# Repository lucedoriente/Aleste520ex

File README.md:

# Aleste 520EX — Western Through-Hole (THT) Complete System (KiCad 9.0)

🌐 **Language / Lingua**: **🇬🇧 English** | [**🇮🇹 Leggi in Italiano (`README.it.md`)**](README.it.md)

---

Complete Western hardware reproduction of the **1993 Soviet Aleste 520EX** Z80 personal computer (an Amstrad CPC 6128 & MSX2 compatible hybrid architecture designed by Patisonic in Omsk, Russia), completely redesigned in **KiCad 9.0** using **100% Western Through-Hole (THT)** components, complete with its dedicated **Cherry MX Mechanical Keyboard (`keyboard/`)** and **Parametric Anti-Flex Enclosure (`case/`)**.

---

## 1. Repository Structure

The repository is organized into four modular directories:

| Directory | Contents | Description |
| :--- | :--- | :--- |
| **[`board/`](board/)** | `Aleste520v4.kicad_pro`, `.kicad_sch`, `.kicad_pcb`, `Componenti_Aleste520v4.csv` | **Motherboard (`400.9 × 280.5 mm`)**: 100% Western THT ICs (`U1..U89`), standard `2.54 mm` `2x06` keyboard headers (`X8`, `X9`), 11 `M3` mounting holes (`MH1..MH11`), labeled power/RTC pads (`P1..P8`), **0 ERC / 0 DRC errors**. |
| **[`keyboard/`](keyboard/)** | `Aleste520_Keyboard.kicad_pro`, `.kicad_sch`, `.kicad_pcb`, `Componenti_Tastiera_Aleste520.csv`, [`README.md`](keyboard/README.md) | **Mechanical Keyboard (`358.0 × 122.0 mm`)**: 82 Cherry MX switches (`SW1..SW81` matrix + `SW82` Hardware Reset), 81 `1N4148` anti-ghosting diodes (Full NKRO), standard `2.54 mm` `2x06` IDC headers (`J1`, `J2`), 10 `M3` anti-flex mounting holes (`MH1..MH10`), **0 ERC / 0 DRC errors**. |
| **[`case/`](case/)** | `Aleste520_Case.FCStd`, `Aleste520_Case.step`, `keyboard_plate.dxf`, [`README.md`](case/README.md) | **Custom Desktop Enclosure (`416.0 × 296.0 × 62.0 mm`)**: Native FreeCAD 1.1 3D CAD project (`Aleste520_Case.FCStd`, `Aleste520_Bottom_Case.FCStd`, `Aleste520_Top_Cover.FCStd`, `Aleste520_Switch_Plate.FCStd`, `Aleste520_Case.step`) (Bottom Base Tray, Sloped Top Cover, `1.5 mm` Switch Mounting Plate, and 4-quadrant split mode for standard $256\times 256\text{ mm}$ 3D printers) + laser-cut ready `keyboard_plate.dxf` with a **3-Stage Anti-Flex Keyboard Support System**. |
| **[`rom/`](rom/)** | `AL512.BIN`, `RFCOLDAT.BIN`, `RFVDKEY.BIN`, `MAPPER.BIN`, `ROMRAM.BIN`, `AF.BIN` | **Original Firmware Images**: 100% bit-compatible with this Western hardware reproduction (English boot menu, standard ASCII/Latin + Cyrillic support). |

---

## 2. Motherboard Highlights (`board/`)

* **100% Western IC Conversion (`U1..U89`)**:
  * All Soviet logic, memory, and peripheral ICs have been converted to standard Western equivalents (`74LSxx`, `74HCxx`, `Z80CPU`, `8255`, `8253`, `8251A`, `8272`, `MC6845`, `AY-3-8910`, `MC146818P`, `HM50256P-20` / `41256`).
  * **Resolved `KR1802IR1` (`КР1802ИР1`)**: Replaced the scarce Soviet 24-pin 16×4 two-port register file ICs at `U60`, `U61`, `U82`, and `U83` with the Western **AMD `AM29705` (DIP-28)**, properly wiring its dual address buses (`A0..A3`, `B0..B3`), write strobes (`~WE1`, `~WE2`), transparent output latches (`~A-LO = GND`, `LE = VCC`), and open-collector outputs (`~OE-A`) for both the color palette (`U60`+`U61`) and keyboard/mapper subsystem (`U82`+`U83`).
  * Standardized all IC reference designators from Russian `D1..D89` to Western `U1..U89`.
* **Upgraded Standard $2.54\text{ mm}$ Keyboard Connectors (`X8` & `X9`)**:
  * Replaced the obsolete single-row $1.27\text{ mm}$ pitch headers on `X8` and `X9` with standard **$2.54\text{ mm}$ ($0.1''$) dual-row `2x06` Pin Headers / IDC Box Headers** (`Connector_PinHeader_2.54mm:PinHeader_2x06_P2.54mm_Vertical`), compatible with standard 12-pin $1.27\text{ mm}$ flat ribbon IDC cables or DuPont harnesses.
* **11 Mechanical `M3` Mounting Holes (`MH1..MH11`)**:
  * Added 11 plated `M3` ($\varnothing\ 3.2\text{ mm}$ drill, $\varnothing\ 6.0\text{ mm}$ pad tied to `GND` chassis shield) mounting holes along the perimeter, center, and front keyboard zone to bolt the motherboard to the enclosure standoffs and coaxial keyboard anti-flex support towers.
* **Fully Routed 2-Layer PCB (`400.9 × 280.5 mm`)**:
  * **0 ERC Errors** across the hierarchical schematic (`board/Aleste520v4.kicad_sch` + 6 sub-sheets).
  * **0 DRC Violations & 0 Unconnected Items** on the PCB (`board/Aleste520v4.kicad_pcb`).
  * Full `F.Cu` and `B.Cu` `GND` copper pours with **Thermal Reliefs** (`0.35 mm` spokes, `0.25 mm` gap) and over **3,670 GND stitching vias**, plus 95 local `100 nF` decoupling capacitors (`C32..C128`).

---

## 3. Power Supply Guide: PicoPSU + $220\text{ V AC} \rightarrow 12\text{ V DC}$

The Aleste 520EX motherboard is powered primarily by **`+5V DC`** (`VCC` plane, consuming $\approx 2.2\text{ A} \dots 2.8\text{ A}$ for the 89 TTL/CMOS/NMOS ICs) plus **`+12V DC`** (routed to the expansion slot `X1` and video connector `X5.B1`), while a separate **`3V` Lithium Coin Cell (`CR2032`)** backs up the `MC146818P` Real-Time Clock (`U19`).

### 3.1 Safe Connection to $220\text{ V AC}$ Mains
For complete electrical safety (eliminating any high-voltage $220\text{ V AC}$ inside the 3D-printed enclosure):
1. **External AC/DC Brick ($220\text{ V AC} \rightarrow 12\text{ V DC}$)**: Use a certified external **`12V DC / 5A (60W)`** switching power adapter with a standard `5.5 × 2.5 mm` DC barrel plug.
2. **Internal DC-DC PicoPSU (`PicoPSU-80` / `PicoPSU-120` or `12V->5V 5A` Buck)**:
   * Mount the panel-mount `5.5 × 2.5 mm` DC barrel jack and optional rocker switch into the dedicated rear cutouts provided in [`case/Aleste520_Case.FCStd`](case/Aleste520_Case.FCStd).
   * Connect the `PS_ON#` (Green wire, Pin 16 on the ATX 24-pin header) of the PicoPSU to `GND` (Black wire, Pin 15/17) via the rear power switch so the PicoPSU turns on when switched.
   * Feed `+5V` and `+12V` from the PicoPSU (using the 4-pin Molex / SATA power cable or ATX header) to the motherboard pads `P1..P6` as detailed below.

### 3.2 Motherboard Power & RTC Battery Pads (`P1..P8`)

| Pad | Silkscreen Label | Net | PCB Coordinates `(X, Y)` | Connection |
| :--- | :--- | :--- | :--- | :--- |
| **`P1`** | `+5V_VCC` | `VCC` (`+5V`) | `(321.31, 240.03)` | **PicoPSU `+5V` (Red wire, 18 AWG)** — Main logic supply |
| **`P2`** | `GND_PWR` | `GND` | `(311.15, 250.19)` | **PicoPSU `GND` (Black wire, 18 AWG)** — Main ground return |
| **`P3`** | `+12V_EXP` | `+12V` | `(303.53, 250.19)` | **PicoPSU `+12V` (Yellow wire)** — Expansion slot `X1` & `X5.B1` |
| **`P4`** | `GND_EXP` | `GND` | `(295.91, 250.19)` | **PicoPSU `GND` (Black wire)** — Auxiliary ground return |
| **`P5`** | `+5V_AUX` | `VCC` (`+5V`) | `(292.10, 260.35)` | **PicoPSU `+5V` (Red wire)** — Parallel `+5V` feed (reduces voltage drop) |
| **`P6`** | `GND_AUX` | `GND` | `(306.07, 265.43)` | **PicoPSU `GND` (Black wire)** — Parallel `GND` feed |
| **`P7`** | `BAT+_3V` | `3V` (`MC146818` RTC) | `(330.20, 232.41)` | **`CR2032` Coin Cell Holder `+` (Positive)** — RTC CMOS backup **(`3V` ONLY!)** |
| **`P8`** | `BAT-_GND` | `GND` | `(330.20, 226.06)` | **`CR2032` Coin Cell Holder `-` (Negative)** — RTC ground |

---

## 4. Dedicated Mechanical Keyboard (`keyboard/`)

See [**`keyboard/README.md`**](keyboard/README.md) for the complete keyboard documentation, matrix table, and pinout.

* **PCB Dimensions**: `358.0 × 122.0 mm` (2-layer FR4, `1.6 mm`, **0 ERC / 0 DRC violations**).
* **Switches**: 81 Cherry MX keys (`SW1..SW81`) arranged in the native $11 \times 8$ Aleste 520EX matrix (`KM0..KM10` $\times$ `KM11..KM18`) + 1 Cherry MX Hardware Reset key (`SW82`, `SBRES` $\rightarrow$ `GND`).
* **Full NKRO Anti-Ghosting**: 81 through-hole `1N4148` diodes (`D1..D81`, `DO-35`) with cathode (`Pin 1`) on column `KM0..KM10` and anode (`Pin 2`) on switch `Pin 1` (matched to the active-low column strobe driven by `74LS145` `U80`).
* **1:1 Ribbon Cable Connection**: Two `2x06` ($2.54\text{ mm}$ pitch) headers `J1` and `J2` connect straight to motherboard headers `X8` and `X9`.

---

## 5. Custom Enclosure with Anti-Flex Keyboard Support (`case/`)

See [**`case/README.md`**](case/README.md) for printing, laser-cutting, and assembly instructions.

* **External Dimensions**: `416.0 × 296.0 × 62.0 mm` (wedged profile: `32 mm` front typing height, `62 mm` rear I/O panel height).
* **3-Stage Anti-Flex Keyboard Support System** (eliminating typing deflection across the $358\text{ mm}$ span):
  1. **`1.5 mm` Rigid Switch Mounting Plate** (`case/keyboard_plate.dxf` for laser-cut aluminum/steel/FR4, or 3D-printed from `case/Aleste520_Switch_Plate.FCStd`).
  2. **Orthogonal Internal Stiffening Grid** built into the underside of the Top Cover (`4.0 × 8.0 mm` perimeter ledge + 2 transverse ribs + 2 longitudinal ribs).
  3. **7 Coaxial Anti-Flex Support Columns (`MH5..MH11`)** transferring vertical typing force straight through the Keyboard PCB (`MH1..MH10`) and Motherboard (`MH5..MH11`) down to the Bottom Case floor.

---

## 6. EPROM & Bipolar PROM Programming Guide (`rom/`)

All 6 original binary files in the [`rom/`](rom/) directory are **100% bit-for-bit compatible** with this Western PCB: no address or data lines were swapped during PCB layout, and the `AM29705` replacements (`U60`, `U61`, `U82`, `U83`) operate in non-inverting transparent mode identical to the original `KR1802IR1`.

> **🇬🇧 Note on Language**: The `rom/AL512.BIN` firmware already features its built-in **English boot/setup interface** (`ALESTE 520EX`, `PATISONIC 1993`, `SETUP`) and includes both standard **Western Latin/ASCII** and Cyrillic character sets (`RUS/LAT` key).

### 6.1 Firmware Mapping Table

| Binary File | Size | PCB Socket | Western IC (Target) | Compatible Equivalents | Original Soviet IC | Function |
| :--- | :--- | :--- | :--- | :--- | :--- | :--- |
| [`rom/AL512.BIN`](rom/AL512.BIN) | `65,536 B` (64 KB) | **`U31`** | **`27C512`** (DIP-28) | `M27C512`, `AM27C512`, `W27C512` (EEPROM) | `К573РФ4` (`K573RF4`) | System BIOS, BASIC, Boot & AMSDOS |
| [`rom/RFCOLDAT.BIN`](rom/RFCOLDAT.BIN) | `2,048 B` (2 KB) | **`U62`** | **`2716` / `27C16`** (DIP-24) | `TMS27C16`, `M2716`, **`AT28C16`** (EEPROM) | `К573РФ2` (`K573RF2`) | Color Palette Lookup (`XD0..XD5`, `VRAMACC`) |
| [`rom/RFVDKEY.BIN`](rom/RFVDKEY.BIN) | `2,048 B` (2 KB) | **`U65`** | **`2716` / `27C16`** (DIP-24) | `TMS27C16`, `M2716`, **`AT28C16`** (EEPROM) | `К573РФ2` (`K573RF2`) | Video Sync (`SYNC*`, `HY*`, `SINT*`) & Keyboard Scan (`KK0..KK3`) |
| [`rom/MAPPER.BIN`](rom/MAPPER.BIN) | `256 B` (`256×4` bit) | **`U28`** | **`AM27S20`** (DIP-16 OC) | `N82S129`, `SN74S287`, `MMI6301`, `MB7052` | `КР556РТ4` (`KR556RT4`) | Memory Bank Address Mapper (`MAP14..MAP17`) |
| [`rom/ROMRAM.BIN`](rom/ROMRAM.BIN) | `256 B` (`256×4` bit) | **`U67`** | **`AM27S20`** (DIP-16 OC) | `N82S129`, `SN74S287`, `MMI6301`, `MB7052` | `КР556РТ4` (`KR556RT4`) | Bus & Memory Enable Decoder (`/ROMEN`, `/RAMEN`, `BUFFER0..1`) |
| [`rom/AF.BIN`](rom/AF.BIN) | `32 B` (`32×8` bit) | **`U69`** | **`SN74188`** (DIP-16 OC) | `N82S23`, `AM27S18`, `MMI6330`, `TBP18SA030` | `К155РЕ3` (`K155RE3`) | Floppy Disk Controller State / Precompensation PROM |

> **⚠️ Critical Note on Output Type (`U28`, `U67`, `U69`)**: The original schematic uses **Open-Collector (OC)** bipolar PROMs (`82S129` / `AM27S20` for `U28`, `U67` and `82S23` / `SN74188` for `U69`). For `U28` (`MAPPER.BIN`), pin 13 (`CS1`) is driven by `/MAPBLK` and the outputs `MAP14..MAP17` are wire-ORed with open-collector register files `U87`/`U88` (`74LS170`), so **`U28` MUST be an Open-Collector part** (`AM27S20` / `82S129` / `74S287`, **not** the totem-pole `82S126` / `74S387` / `AM27S21`).

### 6.2 Required Materials & Tools

* **For the 3 MOS EPROMs / EEPROMs (`U31`, `U62`, `U65`)**:
  * **1× `27C512` (DIP-28, $\le 150\text{ ns}$)** for **`U31`** (e.g., Winbond `W27C512-45Z` EEPROM or ST `M27C512-10F1`).
  * **2× `AT28C16-15PC` (DIP-24 EEPROM, 150 ns)** or fast CMOS `27C16` for **`U62`** and **`U65`** (`AT28C16` is 100% plug-and-play in `U62`/`U65` because Pin 21 is tied to `+5V`, and programs at 5V on any USB programmer such as **XGecu TL866II Plus / T48 / T56**).
* **For the 3 Bipolar Fuse-Link PROMs (`U28`, `U67`, `U69`)**:
  * **2× `82S129` / `AM27S20` / `SN74S287` (DIP-16, 256×4 OC)** for **`U28`** and **`U67`**.
  * **1× `82S23` / `SN74188` / `AM27S18` (DIP-16, 32×8 OC)** for **`U69`**.
  * **Programmer**: Industrial programmer supporting bipolar fuse PROMs (**Data I/O**, **Hi-Lo ALL-03/07/11**, **Elnec BeeProg**, **Stag PP39/42**) or an open-source **Arduino Bipolar PROM Programmer**.

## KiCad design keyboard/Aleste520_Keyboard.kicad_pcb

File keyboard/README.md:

# Aleste 520EX — Staggered Mechanical Keyboard Subsystem (`keyboard/`)

This directory contains the complete KiCad 9.0 schematic, routed 2-layer PCB, 3D switch/stabilizer models, and Bill of Materials for the **Aleste 520EX Staggered Mechanical Keyboard** (`358.0 × 122.0 mm`), reverse-engineered directly from the hardware keyboard scan EPROM ([`rom/RFVDKEY.BIN`](../rom/RFVDKEY.BIN), IC `U65`) and system BIOS ([`rom/AL512.BIN`](../rom/AL512.BIN), offset `0x1EEF`).

---

## 1. Files in `keyboard/`

- **[`Aleste520_Keyboard.kicad_pro`](Aleste520_Keyboard.kicad_pro)**: KiCad 9.0 project file.
- **[`Aleste520_Keyboard.kicad_sch`](Aleste520_Keyboard.kicad_sch)**: Complete electrical schematic (`0 ERC errors/warnings`) with 82 staggered matrix keys (`SW1..SW82`), 82 `1N4148` anti-ghosting diodes (`D1..D82`), 1 hardware reset key (`SW83`), and dual `2x06` (`2.54 mm`) IDC connectors (`J1`, `J2`).
- **[`Aleste520_Keyboard.kicad_pcb`](Aleste520_Keyboard.kicad_pcb)**: Fully routed 2-layer PCB (`358.0 × 122.0 mm`, **0 DRC violations, 0 unconnected pads**) featuring:
  - Authentic staggered physical key layout with **`6.25U` (`119.06 mm`) Spacebar (`SW81`)** and PCB-mount Cherry MX stabilizer holes at `±50.0 mm` (`Button_Switch_Keyboard:SW_Cherry_MX_6.25u_PCB`).
  - Staggered modifier footprints (`1.50U TAB`, `1.75U CAPS`, `2.00U SHIFT`, `1.50U RETURN`, `1.50U CTRL`, `1.25U RUS/LAT`, `1.25U COPY`, `1.50U GRAPH`, and `1.25U` top function keys).
  - Separate right-hand Numpad & Cursor block (`F0..F9`, `FDOT`, `ENTER`, `UP/DOWN/LEFT/RIGHT`) and isolated top-right `RESET` key (`SW83`).
  - Centered top silkscreen title between `MH2 (124.0, 4.0)` and `MH3 (244.0, 4.0)`.
  - 10 `M3` (`3.2 mm` drill) anti-flex mounting holes (`MH1..MH10`) placed completely outside all keycap skirts.
- **[`3dmodels/`](3dmodels/)**: Colored VRML 2.0 and STEP 3D models for all Cherry MX key widths (`1.00u`, `1.25u`, `1.50u`, `1.75u`, `2.00u`, and `6.25u` with stabilizers and wire).
- **[`keyboard_top.png`](keyboard_top.png)** & **[`keyboard_bottom.png`](keyboard_bottom.png)**: Raytraced 3D renders of the populated keyboard PCB.
- **[`Componenti_Tastiera_Aleste520.csv`](Componenti_Tastiera_Aleste520.csv)**: Complete Bill of Materials (BOM).

---

## 2. Decoded Hardware Keyboard Matrix (`KM0..KM10 × KM11..KM18`)

On the Aleste 520EX motherboard, counter `U63` and `2716` EPROM `U65` (`RFVDKEY.BIN`) drive 74LS154 4-to-16 column demultiplexer `U80` (`KM0..KM10`, active-low) and 74LS151 8-to-1 row multiplexer `U81` (`KM11..KM18`), shifting the scanned state into `U84` (`74LS374`) to emulate the Amstrad CPC / MSX keyboard matrix on `AY-3-8910` (`U18`) Port A (`X1..X8`).

| Column \ Row | `KM11` (`D0`) | `KM12` (`D1`) | `KM13` (`D2`) | `KM14` (`D3`) | `KM15` (`D4`) | `KM16` (`D5`) | `KM17` (`D6`) | `KM18` (`D7`) |
| :--- | :---: | :---: | :---: | :---: | :---: | :---: | :---: | :---: |
| **`KM0`** | — | — | — | — | **`SHIFT`** (`2.00U`) | `F7` | `F8` | `F9` |
| **`KM1`** | **`ESC`** | **`TAB`** (`1.50U`) | **`CTRL`** (`1.50U`) | **`RUS/LAT`** (`1.25U`) | **`CAPS`** (`1.75U`) | `F0` | `FDOT` (`.`) | `ENTER` (Num) |
| **`KM2`** | `;` (`+`) | `J` | `F` | `Q` | **`COPY`** (`1.25U`) | `F1` | `F2` | `F3` |
| **`KM3`** | `F1_MSX` (`1.25U`) | `1` (`!`) | `C` | `Y` | `^` (`£`) | `F4` | `F5` | `F6` |
| **`KM4`** | `F2_MSX` (`1.25U`) | `2` (`"`) | `U` | `W` | `S` | — | **`CLR`** (`1.25U`) | — |
| **`KM5`** | `F3_MSX` (`1.25U`) | `3` (`#`) | `K` | `A` | `M` | **`DEL`** (`1.25U`) | **`STOP`** (`1.25U`) | **`SELECT`** (`1.25U`) |
| **`KM6`** | `4` (`$`) | `E` | `P` | `I` | **`SPACE`** (**`6.25U`**) | `RIGHT` (`→`) | **`RETURN`** (`1.50U`) | **`GRAPH`** (`1.50U`) |
| **`KM7`** | `F4_MSX` (`1.25U`) | `5` (`%`) | `N` | `R` | `T` | `DOWN` (`↓`) | `UP` (`↑`) | `/` (`?`) |
| **`KM8`** | `F5_MSX` (`1.25U`) | `6` (`&`) | `G` | `O` | `X` | `.` (`>`) | `:` (`*`) | `-` (`=`) |
| **`KM9`** | `7` (`'`) | `[` (`{`) | `L` | `B` | `LEFT` (`←`) | `\` (`` ` ``) | `H` | `0` (`_`) |
| **`KM10`** | `8` (`(`) | `]` (`}`) | `D` | `@` (`\|`) | `,` (`<`) | `V` | `Z` | `9` (`)`) |

---

## 3. Staggered Physical Layout & Keycap Sizes

- **Row 0 (`Y = 26.0 mm` — Function & System Control Row)**:
  - `ESC (1.00U)` | `F1 (1.25U)` `F2 (1.25U)` `F3 (1.25U)` `F4 (1.25U)` `F5 (1.25U)` | `SELECT (1.25U)` `STOP (1.25U)` `CLR (1.25U)` `DEL (1.25U)` | isolated `RESET (1.00U)` at `X = 339.5 mm`
- **Row 1 (`Y = 43.5 mm` — Number Row + Numpad Row 1)**:
  - `1` `2` `3` `4` `5` `6` `7` `8` `9` `0` `-` `^` `\` (all `1.00U`) || `F7` `F8` `F9` `UP` (`1.00U`)
- **Row 2 (`Y = 61.0 mm` — QWERTY Row + Numpad Row 2)**:
  - `TAB (1.50U)` `Q` `W` `E` `R` `T` `Y` `U` `I` `O` `P` `@` `[` || `F4` `F5` `F6` `DOWN` (`1.00U`)
- **Row 3 (`Y = 78.5 mm` — Home Row + Numpad Row 3)**:
  - `CAPS (1.75U)` `A` `S` `D` `F` `G` `H` `J` `K` `L` `;` `:` `]` || `F1` `F2` `F3` `LEFT` (`1.00U`)
- **Row 4 (`Y = 96.0 mm` — Shift Row + Numpad Row 4)**:
  - `SHIFT (2.00U)` `Z` `X` `C` `V` `B` `N` `M` `,` `.` `/` `RETURN (1.50U)` || `F0` `FDOT` `ENTER` `RIGHT` (`1.00U`)
- **Row 5 (`Y = 113.5 mm` — Bottom Spacebar Row)**:
  - `CTRL (1.50U)` `RUS/LAT (1.25U)` `COPY (1.25U)` **`SPACE (6.25U, 119.06 mm with ±50.0 mm Cherry MX stabilizers)`** `GRAPH (1.50U)`

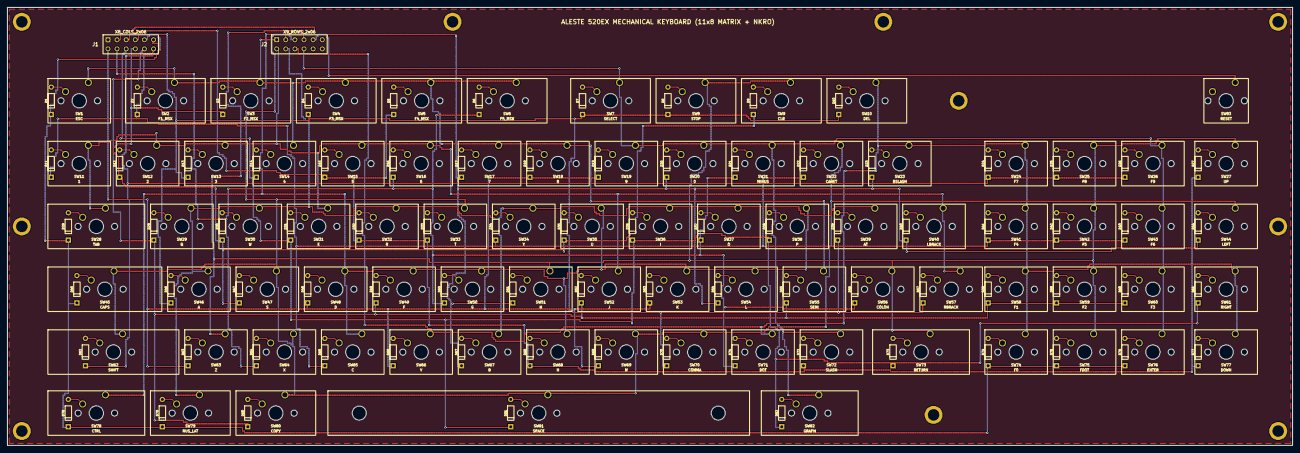
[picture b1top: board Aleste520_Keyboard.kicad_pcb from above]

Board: 2 copper layers, 358.0 x 122.0 mm, 177 parts (0 on the bottom side), 103 nets.

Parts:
D1, D2, D3, D4, D5, D6, D7, D8, D9, D10, D11, D12, D13, D14, D15, D16, D17, D18, D19, D20, D21, D22, D23, D24, D25, D26, D27, D28, D29, D30, D31, D32, D33, D34, D35, D36, D37, D38, D39, D40, D41, D42, D43, D44, D45, D46, D47, D48, D49, D50, D51, D52, D53, D54, D55, D56, D57, D58, D59, D60, D61, D62, D63, D64, D65, D66, D67, D68, D69, D70, D71, D72, D73, D74, D75, D76, D77, D78, D79, D80, D81, D82: 1N4148; D_DO-35_SOD27_P7.62mm_Horizontal
J1: X8_COLS_2x06; PinHeader_2x06_P2.54mm_Vertical
J2: X9_ROWS_2x06; PinHeader_2x06_P2.54mm_Vertical
MH1, MH2, MH3, MH4, MH5, MH6, MH7, MH8, MH9, MH10: M3_AntiFlex; MountingHole_3.2mm_M3_Pad
SW1: ESC; SW_Cherry_MX_1.00u_PCB
SW2: F1_MSX; SW_Cherry_MX_1.25u_PCB
SW3: F2_MSX; SW_Cherry_MX_1.25u_PCB
SW4: F3_MSX; SW_Cherry_MX_1.25u_PCB
SW5: F4_MSX; SW_Cherry_MX_1.25u_PCB
SW6: F5_MSX; SW_Cherry_MX_1.25u_PCB
SW7: SELECT; SW_Cherry_MX_1.25u_PCB
SW8: STOP; SW_Cherry_MX_1.25u_PCB
SW9: CLR; SW_Cherry_MX_1.25u_PCB
SW10: DEL; SW_Cherry_MX_1.25u_PCB
SW11: 1; SW_Cherry_MX_1.00u_PCB
SW12: 2; SW_Cherry_MX_1.00u_PCB
SW13: 3; SW_Cherry_MX_1.00u_PCB
SW14: 4; SW_Cherry_MX_1.00u_PCB
SW15: 5; SW_Cherry_MX_1.00u_PCB
SW16: 6; SW_Cherry_MX_1.00u_PCB
SW17: 7; SW_Cherry_MX_1.00u_PCB
SW18: 8; SW_Cherry_MX_1.00u_PCB
SW19: 9; SW_Cherry_MX_1.00u_PCB
SW20: 0; SW_Cherry_MX_1.00u_PCB
SW21: MINUS; SW_Cherry_MX_1.00u_PCB
SW22: CARET; SW_Cherry_MX_1.00u_PCB
SW23: BSLASH; SW_Cherry_MX_1.00u_PCB
SW24: F7; SW_Cherry_MX_1.00u_PCB
SW25: F8; SW_Cherry_MX_1.00u_PCB
SW26: F9; SW_Cherry_MX_1.00u_PCB
SW27: UP; SW_Cherry_MX_1.00u_PCB
SW28: TAB; SW_Cherry_MX_1.50u_PCB
SW29: Q; SW_Cherry_MX_1.00u_PCB
SW30: W; SW_Cherry_MX_1.00u_PCB
SW31: E; SW_Cherry_MX_1.00u_PCB
SW32: R; SW_Cherry_MX_1.00u_PCB
SW33: T; SW_Cherry_MX_1.00u_PCB
SW34: Y; SW_Cherry_MX_1.00u_PCB
SW35: U; SW_Cherry_MX_1.00u_PCB
SW36: I; SW_Cherry_MX_1.00u_PCB
SW37: O; SW_Cherry_MX_1.00u_PCB
SW38: P; SW_Cherry_MX_1.00u_PCB
SW39: AT; SW_Cherry_MX_1.00u_PCB
SW40: LBRACK; SW_Cherry_MX_1.00u_PCB
SW41: F4; SW_Cherry_MX_1.00u_PCB
SW42: F5; SW_Cherry_MX_1.00u_PCB
SW43: F6; SW_Cherry_MX_1.00u_PCB
SW44: LEFT; SW_Cherry_MX_1.00u_PCB
SW45: CAPS; SW_Cherry_MX_1.75u_PCB
SW46: A; SW_Cherry_MX_1.00u_PCB
SW47: S; SW_Cherry_MX_1.00u_PCB
SW48: D; SW_Cherry_MX_1.00u_PCB
SW49: F; SW_Cherry_MX_1.00u_PCB
SW50: G; SW_Cherry_MX_1.00u_PCB
SW51: H; SW_Cherry_MX_1.00u_PCB
SW52: J; SW_Cherry_MX_1.00u_PCB
SW53: K; SW_Cherry_MX_1.00u_PCB
SW54: L; SW_Cherry_MX_1.00u_PCB
SW55: SEMI; SW_Cherry_MX_1.00u_PCB
SW56: COLON; SW_Cherry_MX_1.00u_PCB
SW57: RBRACK; SW_Cherry_MX_1.00u_PCB
SW58: F1; SW_Cherry_MX_1.00u_PCB
SW59: F2; SW_Cherry_MX_1.00u_PCB
SW60: F3; SW_Cherry_MX_1.00u_PCB
SW61: RIGHT; SW_Cherry_MX_1.00u_PCB
SW62: SHIFT; SW_Cherry_MX_2.00u_PCB
SW63: Z; SW_Cherry_MX_1.00u_PCB
SW64: X; SW_Cherry_MX_1.00u_PCB
SW65: C; SW_Cherry_MX_1.00u_PCB
SW66: V; SW_Cherry_MX_1.00u_PCB
SW67: B; SW_Cherry_MX_1.00u_PCB
SW68: N; SW_Cherry_MX_1.00u_PCB
SW69: M; SW_Cherry_MX_1.00u_PCB
SW70: COMMA; SW_Cherry_MX_1.00u_PCB
SW71: DOT; SW_Cherry_MX_1.00u_PCB
SW72: SLASH; SW_Cherry_MX_1.00u_PCB
SW73: RETURN; SW_Cherry_MX_1.50u_PCB
SW74: F0; SW_Cherry_MX_1.00u_PCB
SW75: FDOT; SW_Cherry_MX_1.00u_PCB
SW76: ENTER; SW_Cherry_MX_1.00u_PCB
SW77: DOWN; SW_Cherry_MX_1.00u_PCB
SW78: CTRL; SW_Cherry_MX_1.50u_PCB
SW79: RUS_LAT; SW_Cherry_MX_1.25u_PCB
SW80: COPY; SW_Cherry_MX_1.25u_PCB
SW81: SPACE; SW_Cherry_MX_6.25u_PCB
SW82: GRAPH; SW_Cherry_MX_1.50u_PCB
SW83: RESET; SW_Cherry_MX_1.00u_PCB

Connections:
GND: J1.1, J2.12, MH1.1, MH2.1, MH3.1, MH4.1, MH5.1, MH6.1, MH7.1, MH8.1, MH9.1, MH10.1, SW83.1
KM0: D24.1, D25.1, D26.1, D62.1, J1.12
KM1: D1.1, D28.1, D45.1, D74.1, D75.1, D76.1, D78.1, D79.1, J1.11
KM2: D29.1, D49.1, D52.1, D55.1, D58.1, D59.1, D60.1, D80.1, J1.10
KM3: D2.1, D11.1, D22.1, D34.1, D41.1, D42.1, D43.1, D65.1, J1.9
KM4: D3.1, D9.1, D12.1, D30.1, D35.1, D47.1, J1.8
KM5: D4.1, D7.1, D8.1, D10.1, D13.1, D46.1, D53.1, D69.1, J1.7
KM6: D14.1, D31.1, D36.1, D38.1, D61.1, D73.1, D81.1, D82.1, J1.6
KM7: D5.1, D15.1, D27.1, D32.1, D33.1, D68.1, D72.1, D77.1, J1.5
KM8: D6.1, D16.1, D21.1, D37.1, D50.1, D56.1, D64.1, D71.1, J1.4
KM9: D17.1, D20.1, D23.1, D40.1, D44.1, D51.1, D54.1, D67.1, J1.3
KM10: D18.1, D19.1, D39.1, D48.1, D57.1, D63.1, D66.1, D70.1, J1.2
KM11: J2.1, SW1.2, SW2.2, SW3.2, SW4.2, SW5.2, SW6.2, SW14.2, SW17.2, SW18.2, SW55.2
KM12: J2.2, SW11.2, SW12.2, SW13.2, SW15.2, SW16.2, SW28.2, SW31.2, SW40.2, SW52.2, SW57.2
KM13: J2.3, SW35.2, SW38.2, SW48.2, SW49.2, SW50.2, SW53.2, SW54.2, SW65.2, SW68.2, SW78.2
KM14: J2.4, SW29.2, SW30.2, SW32.2, SW34.2, SW36.2, SW37.2, SW39.2, SW46.2, SW67.2, SW79.2
KM15: J2.5, SW22.2, SW33.2, SW44.2, SW45.2, SW47.2, SW62.2, SW64.2, SW69.2, SW70.2, SW80.2, SW81.2
KM16: J2.6, SW10.2, SW23.2, SW24.2, SW41.2, SW58.2, SW61.2, SW66.2, SW71.2, SW74.2, SW77.2
KM17: J2.7, SW8.2, SW9.2, SW25.2, SW27.2, SW42.2, SW51.2, SW56.2, SW59.2, SW63.2, SW73.2, SW75.2
KM18: J2.8, SW7.2, SW19.2, SW20.2, SW21.2, SW26.2, SW43.2, SW60.2, SW72.2, SW76.2, SW82.2
unnamed: D1.2, SW1.1
unnamed: D2.2, SW2.1
unnamed: D3.2, SW3.1
unnamed: D4.2, SW4.1
unnamed: D5.2, SW5.1
unnamed: D6.2, SW6.1
unnamed: D7.2, SW7.1
unnamed: D8.2, SW8.1
unnamed: D9.2, SW9.1
unnamed: D10.2, SW10.1
unnamed: D11.2, SW11.1
unnamed: D12.2, SW12.1
unnamed: D13.2, SW13.1
unnamed: D14.2, SW14.1
unnamed: D15.2, SW15.1
unnamed: D16.2, SW16.1
unnamed: D17.2, SW17.1
unnamed: D18.2, SW18.1
unnamed: D19.2, SW19.1
unnamed: D20.2, SW20.1
unnamed: D21.2, SW21.1
unnamed: D22.2, SW22.1
unnamed: D23.2, SW23.1
unnamed: D24.2, SW24.1
unnamed: D25.2, SW25.1
unnamed: D26.2, SW26.1
unnamed: D27.2, SW27.1
unnamed: D28.2, SW28.1
unnamed: D29.2, SW29.1
unnamed: D30.2, SW30.1
unnamed: D31.2, SW31.1
unnamed: D32.2, SW32.1
unnamed: D33.2, SW33.1
unnamed: D34.2, SW34.1
unnamed: D35.2, SW35.1
unnamed: D36.2, SW36.1
unnamed: D37.2, SW37.1
unnamed: D38.2, SW38.1
unnamed: D39.2, SW39.1
unnamed: D40.2, SW40.1
unnamed: D41.2, SW41.1
unnamed: D42.2, SW42.1
unnamed: D43.2, SW43.1
unnamed: D44.2, SW44.1
unnamed: D45.2, SW45.1
unnamed: D46.2, SW46.1
unnamed: D47.2, SW47.1
unnamed: D48.2, SW48.1
unnamed: D49.2, SW49.1
unnamed: D50.2, SW50.1
unnamed: D51.2, SW51.1
unnamed: D52.2, SW52.1
unnamed: D53.2, SW53.1
unnamed: D54.2, SW54.1
unnamed: D55.2, SW55.1
unnamed: D56.2, SW56.1
unnamed: D57.2, SW57.1
unnamed: D58.2, SW58.1
unnamed: D59.2, SW59.1
unnamed: D60.2, SW60.1
unnamed: D61.2, SW61.1
unnamed: D62.2, SW62.1
unnamed: D63.2, SW63.1
unnamed: D64.2, SW64.1
unnamed: D65.2, SW65.1
unnamed: D66.2, SW66.1
unnamed: D67.2, SW67.1
unnamed: D68.2, SW68.1
unnamed: D69.2, SW69.1
unnamed: D70.2, SW70.1
unnamed: D71.2, SW71.1
unnamed: D72.2, SW72.1
unnamed: D73.2, SW73.1
unnamed: D74.2, SW74.1
unnamed: D75.2, SW75.1
unnamed: D76.2, SW76.1
unnamed: D77.2, SW77.1
unnamed: D78.2, SW78.1
unnamed: D79.2, SW79.1
unnamed: D80.2, SW80.1
unnamed: D81.2, SW81.1
unnamed: D82.2, SW82.1
SBRES: J2.9, SW83.2
